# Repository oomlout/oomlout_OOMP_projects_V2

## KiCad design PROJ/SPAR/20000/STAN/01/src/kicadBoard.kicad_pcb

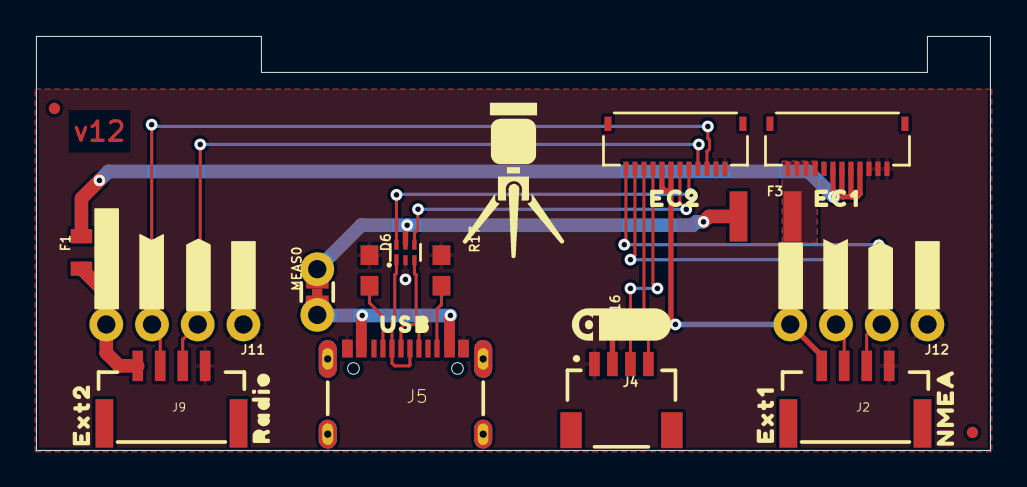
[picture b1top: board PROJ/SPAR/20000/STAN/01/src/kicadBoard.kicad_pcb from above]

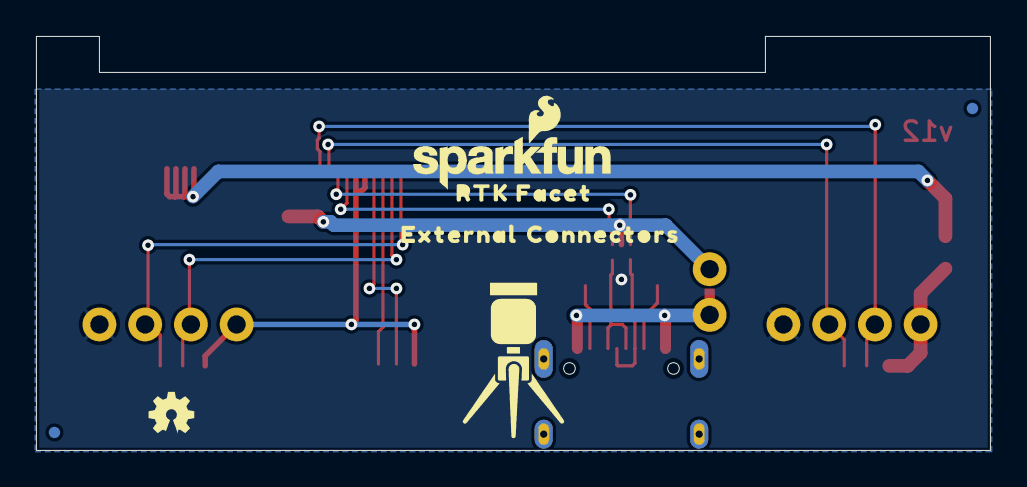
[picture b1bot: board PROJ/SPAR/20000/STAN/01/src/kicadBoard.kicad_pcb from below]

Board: 2 copper layers, 53.0 x 23.0 mm, 42 parts (8 on the bottom side), 19 nets.

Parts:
D6: PRTR5V0U2F; SOT886
F1: 6V 0.5A; 0805
F3: 6V/2A; 1210
FRAME1: FRAME-LETTER; CREATIVE_COMMONS
J1, J6: FPC_12_0.5MM_BACKFLIP; FPC_12_DOUBLESIDED_BACKFLIP
J2, J9: JST-4-SMD-1.25MM-LOCKING
J4: Qwiic Right Angle; JST04_1MM_RA
J5: u-blox USB; USB-C-16P-2LAYER-PADS
J11, J12: 1X04_NO_SILK
JP21, JP61, JP71, JP81: FIDUCIALUFIDUCIAL; FIDUCIAL-MICRO
LOGO1: OSHW-LOGOMINI; OSHW-LOGO-MINI
LOGO2: SFE_LOGO_NAME_FLAME.1_INCH; SFE_LOGO_NAME_FLAME_.1
LOGO3: QWIIC_LOGO_CONNECTOR; QWIIC_5.5MM
MEAS0: COMBO-JUMPER_2_NC_TRACE
R16, R17: 5.1k; 0603
U$1: USB0
U$2: CONNECTORS1
U$3, U$13: RTK5#SVG0
U$4: EXT10
U$5: #3V3#0
U$6: EXT22
U$7: NMEA1
U$8: EC10
U$9: EXTERNAL0
U$11: EC21
U$12: RADIO3
U$14: RTK_FACET0
U$23: #3#5#5V#0
U$38, U$82: #GND#0
U$39: #RX2#2
U$40: #TX2#1
U$65: #TX1#1
U$68: #RX1#2

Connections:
3.3V: J2.1, J4.2, J6.7, J6.8, J12.4
CC1: J5.A5, R17.2
CC2: J5.B5, R16.2
ESP_21/SDA: J4.3, J6.9
ESP_22/SCL: J4.4, J6.10
EXTERNAL_SERIAL1_RXI: J2.3, J6.12, J12.2
EXTERNAL_SERIAL1_TXO: J2.2, J6.11, J12.3
GND: D6.2, J1.1, J1.2, J1.3, J2.4, J4.1, J5.GND, J5.GND2, J5.SHLD1, J5.SHLD2, J5.SHLD3, J5.SHLD4, J6.1, J6.2, J9.4, J11.1, J12.1, R16.1, R17.1
unnamed: F1.1, J9.1, J11.4
USB1_D_M: D6.1, J5.A7, J5.B7
USB1_D_P: D6.3, J5.A6, J5.B6
USB_DM: D6.6, J6.5
USB_DP: D6.4, J6.6
VIN: J5.VBUS1, J5.VBUS2, MEAS0.1, MEAS0.3
VIN1: D6.5, F3.1, MEAS0.2, MEAS0.4
V_BATT: F1.2, J1.4, J1.5, J1.6, J1.7
V_USB: F3.2, J1.9, J1.10, J1.11, J1.12
ZED-RXI2: J6.4, J9.3, J11.2
ZED-TXO2: J6.3, J9.2, J11.3

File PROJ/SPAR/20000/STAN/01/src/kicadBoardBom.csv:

"Id";"Designator";"Package";"Quantity";"Designation";"Supplier and ref";
1;"U$82,U$38";"#GND#0";2;"";;;
2;"R17,R16";"0603";2;"5.1k";;;
3;"J11,J12";"1X04_NO_SILK";2;"";;;
4;"U$12";"RADIO3";1;"";;;
5;"F1";"0805";1;"6V 0.5A";;;
6;"MEAS0";"COMBO-JUMPER_2_NC_TRACE";1;"";;;
7;"U$68";"#RX1#2";1;"";;;
8;"D6";"SOT886";1;"PRTR5V0U2F";;;
9;"LOGO3";"QWIIC_5.5MM";1;"QWIIC_LOGO_CONNECTOR";;;
10;"J9,J2";"JST-4-SMD-1.25MM-LOCKING";2;"";;;
11;"J1,J6";"FPC_12_DOUBLESIDED_BACKFLIP";2;"FPC_12_0.5MM_BACKFLIP";;;
12;"U$39";"#RX2#2";1;"";;;
13;"FRAME1";"CREATIVE_COMMONS";1;"FRAME-LETTER";;;
14;"U$8";"EC10";1;"";;;
15;"J5";"USB-C-16P-2LAYER-PADS";1;"u-blox USB";;;
16;"U$11";"EC21";1;"";;;
17;"JP21,JP61,JP71,JP81";"FIDUCIAL-MICRO";4;"FIDUCIALUFIDUCIAL";;;
18;"U$23";"#3#5#5V#0";1;"";;;
19;"U$40";"#TX2#1";1;"";;;
20;"U$5";"#3V3#0";1;"";;;
21;"U$3,U$13";"RTK5#SVG0";2;"";;;
22;"J4";"JST04_1MM_RA";1;"Qwiic Right Angle";;;
23;"U$65";"#TX1#1";1;"";;;
24;"U$4";"EXT10";1;"";;;
25;"U$1";"USB0";1;"";;;
26;"U$6";"EXT22";1;"";;;
27;"F3";"1210";1;"6V/2A";;;
28;"U$7";"NMEA1";1;"";;;
29;"LOGO2";"SFE_LOGO_NAME_FLAME_.1";1;"SFE_LOGO_NAME_FLAME.1_INCH";;;
30;"U$2";"CONNECTORS1";1;"";;;
31;"U$14";"RTK_FACET0";1;"";;;
32;"LOGO1";"OSHW-LOGO-MINI";1;"OSHW-LOGOMINI";;;
33;"U$9";"EXTERNAL0";1;"";;;

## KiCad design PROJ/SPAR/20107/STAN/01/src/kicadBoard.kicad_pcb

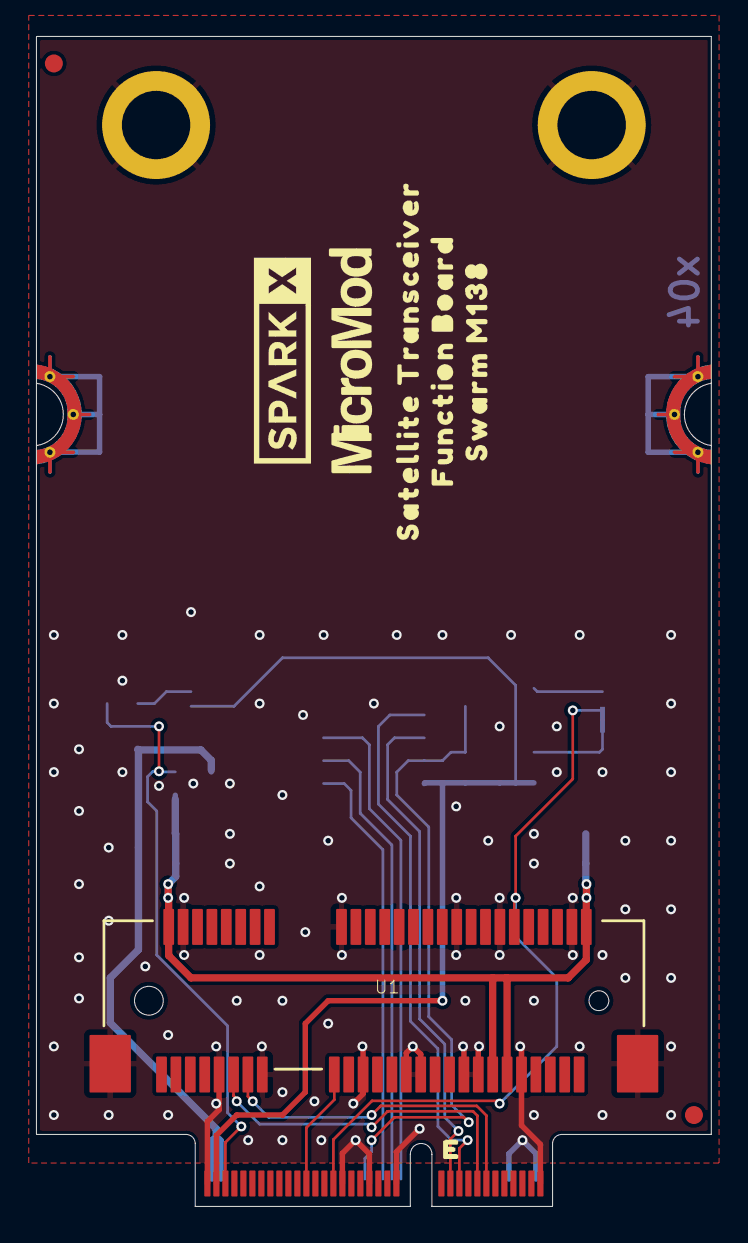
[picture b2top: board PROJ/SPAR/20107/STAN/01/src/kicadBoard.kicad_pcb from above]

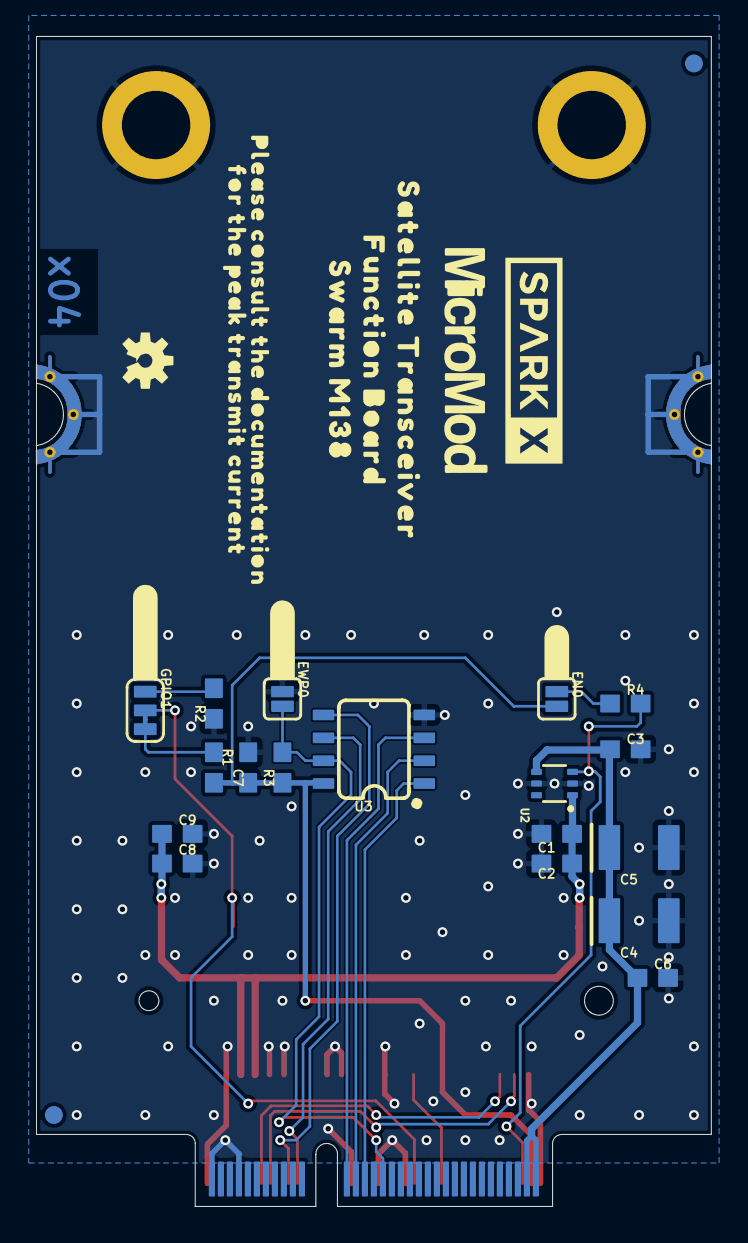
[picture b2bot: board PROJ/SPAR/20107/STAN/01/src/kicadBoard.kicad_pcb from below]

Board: 2 copper layers, 37.5 x 65.0 mm, 44 parts (31 on the bottom side), 18 nets.

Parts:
C1, C9: 10uF; 0603
C2, C3, C6, C7, C8: 0.1uF; 0603
C4, C5: 100uF; EIA3528
EN0: JUMPER-SMT_2_NO_SILK; SMT-JUMPER_2_NO_SILK
EWP0: JUMPER-SMT_2_NO_SILK; SMT-JUMPER_2_NO_SILK
FD1, FD2, FD3, FD4: FIDUCIAL1X2; FIDUCIAL-1X2
FRAME1: FRAME-LETTER; CREATIVE_COMMONS
GPIO1: JUMPER-SMT_3_1-NC_TRACE_SILK; SMT-JUMPER_3_1-NC_TRACE_SILK
H5, H6: STAND-OFF-REFLOW-M2.5_1.5MM_TALL; STAND-OFF-REFLOW-M2.5
J3: MICROMOD_FUNCTION_STANDARD; M.2-CARD-E-22_FUNCTION_STANDARD
LOGO1: SPECIAL_INSTRUCTIONS-ORDERING; ORDERING_INSTRUCTIONS
LOGO2: OSHW-LOGOS; OSHW-LOGO-S
R1, R2, R3, R4: 100k; 0603
U1: SWARM_M138_TRANSCEIVER_MAIN; M.2-SWARM-M138-A
U2: MIC94064YC6; SC-70-6
U3: EEPROM; SO08
U$1, U$2: SPARKX-LOGO5; SPARKX-LARGE
U$3, U$7: FUNCTION_BOARD0
U$4, U$5: SATELLITE_TRANSCEIVER0
U$6: PLEASE_CONSULT_THE_DOCUMENTATION0
U$8: #EWP#0
U$9, U$10: MICROMOD_LOGO_.5
U$11: #EN#0
U$19: #GPIO1#0
U$31: FOR_THE_PEAK_TRANSMIT_CURRENT1
U$40, U$41: SWARM_M1381

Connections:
3.3V: C7.1, EN0.2, J3.73, R1.2, R3.1, U3.8
A0: J3.36, U3.1
A1: J3.34, U3.2
A2: J3.32, U3.3
EWP: EWP0.2, J3.40, R3.2, U3.7
GND: C1.2, C2.2, C3.2, C4.C, C5.C, C6.2, C7.2, C8.2, C9.2, EWP0.1, H5.1, H6.1, J3.1, J3.2, J3.8, J3.33, J3.39, J3.45, J3.75, J3.GND1, J3.GND2, J3.GND3, J3.GND4, J3.GND5, J3.GND6, R2.1, U1.4, U1.9, U1.15, U1.18, U1.21, U1.26, U1.27, U1.29, U1.34, U1.35, U1.37, U1.40, U1.43, U1.50, U1.A1, U1.A2, U2.2, U2.5, U3.4
GPIO1: GPIO1.2, J3.47, U1.42
unnamed: EN0.1, R4.1
unnamed: GPIO1.3, R1.1
unnamed: GPIO1.1, R2.2
PWR_EN: J3.71, R4.2, U2.3
RXI: J3.15, U1.11
SCL: J3.21, U3.6
SDA: J3.19, U3.5
TX/~RX: J3.53, U1.17
TXO: J3.13, U1.13
VCC: C3.1, C4.A, C5.A, C6.1, J3.72, J3.74, U2.4
VIN: C1.1, C2.1, C8.1, C9.1, U1.2, U1.39, U1.41, U1.52, U2.1

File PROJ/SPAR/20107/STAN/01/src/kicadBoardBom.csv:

"Id";"Designator";"Package";"Quantity";"Designation";"Supplier and ref";
1;"H6,H5";"STAND-OFF-REFLOW-M2.5";2;"STAND-OFF-REFLOW-M2.5_1.5MM_TALL";;;
2;"FD1,FD3,FD4,FD2";"FIDUCIAL-1X2";4;"FIDUCIAL1X2";;;
3;"J3";"M.2-CARD-E-22_FUNCTION_STANDARD";1;"MICROMOD_FUNCTION_STANDARD";;;
4;"LOGO1";"ORDERING_INSTRUCTIONS";1;"SPECIAL_INSTRUCTIONS-ORDERING";;;
5;"U$40,U$41";"SWARM_M1381";2;"";;;
6;"U$9,U$10";"MICROMOD_LOGO_.5";2;"";;;
7;"FRAME1";"CREATIVE_COMMONS";1;"FRAME-LETTER";;;
8;"U$2,U$1";"SPARKX-LARGE";2;"SPARKX-LOGO5";;;
9;"U1";"M.2-SWARM-M138-A";1;"SWARM_M138_TRANSCEIVER_MAIN";;;
10;"U$4,U$5";"SATELLITE_TRANSCEIVER0";2;"";;;
11;"U$3,U$7";"FUNCTION_BOARD0";2;"";;;
12;"LOGO2";"OSHW-LOGO-S";1;"OSHW-LOGOS";;;
13;"GPIO1";"SMT-JUMPER_3_1-NC_TRACE_SILK";1;"JUMPER-SMT_3_1-NC_TRACE_SILK";;;
14;"R3,R2,R1,R4";"0603";4;"100k";;;
15;"C3,C7,C6,C8,C2";"0603";5;"0.1uF";;;
16;"U2";"SC-70-6";1;"MIC94064YC6";;;
17;"U$19";"#GPIO1#0";1;"";;;
18;"U$6";"PLEASE_CONSULT_THE_DOCUMENTATION0";1;"";;;
19;"C4,C5";"EIA3528";2;"100uF";;;
20;"EN0,EWP0";"SMT-JUMPER_2_NO_SILK";2;"JUMPER-SMT_2_NO_SILK";;;
21;"U$8";"#EWP#0";1;"";;;
22;"U$31";"FOR_THE_PEAK_TRANSMIT_CURRENT1";1;"";;;
23;"C9,C1";"0603";2;"10uF";;;
24;"U3";"SO08";1;"EEPROM";;;
25;"U$11";"#EN#0";1;"";;;

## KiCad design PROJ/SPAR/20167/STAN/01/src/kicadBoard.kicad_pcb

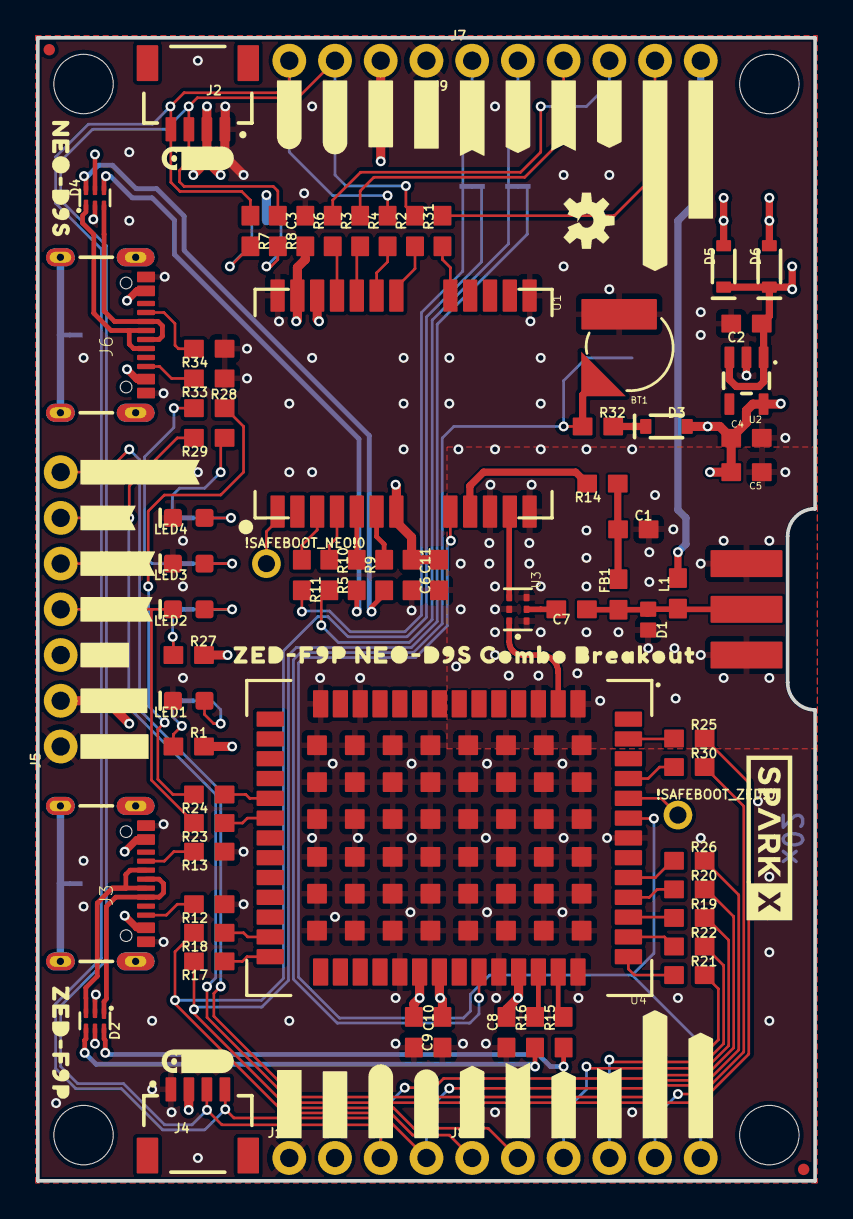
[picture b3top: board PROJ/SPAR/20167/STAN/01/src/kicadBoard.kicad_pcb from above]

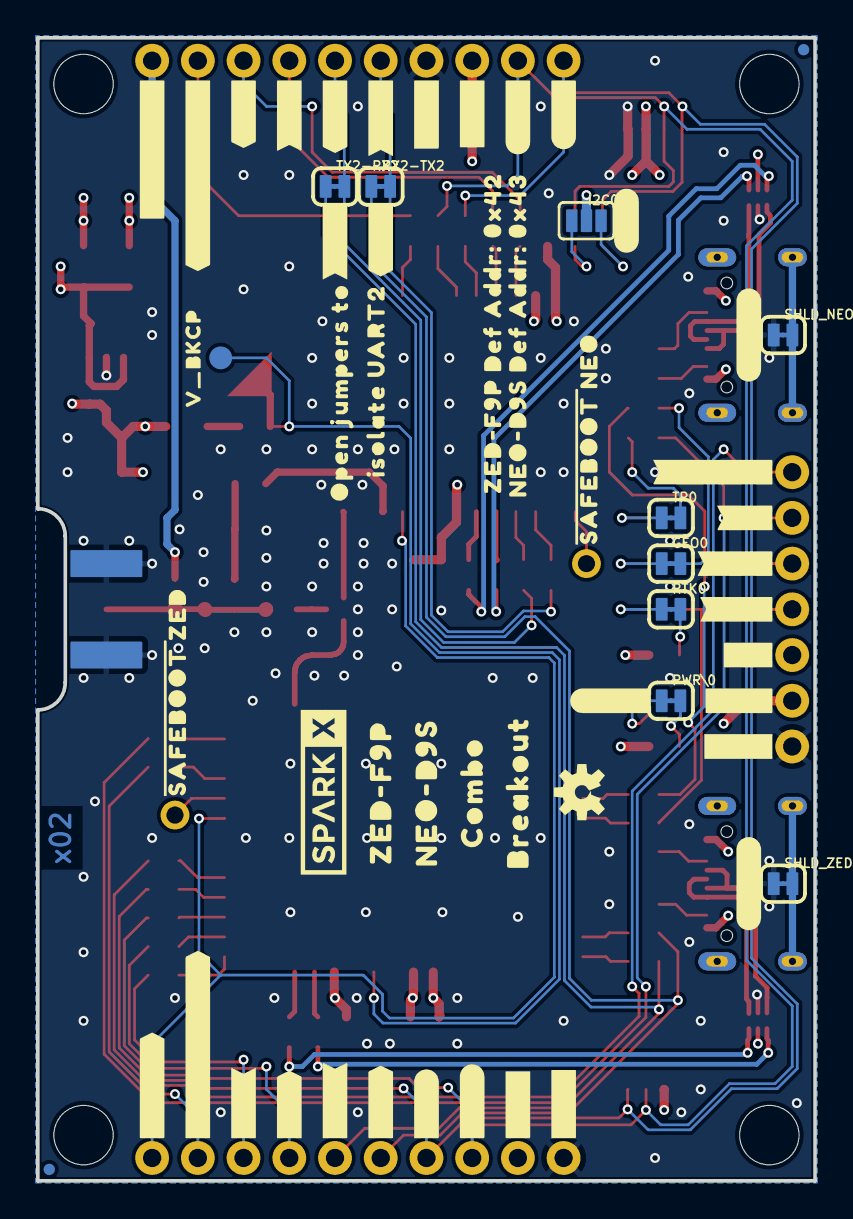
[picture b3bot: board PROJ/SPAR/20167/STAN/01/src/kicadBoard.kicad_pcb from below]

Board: 4 copper layers, 43.2 x 63.5 mm, 174 parts (58 on the bottom side), 79 nets.

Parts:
!SAFEBOOT_NEO!0: TEST-POINTPOGO_PTH; 1X01_NO_SILK
!SAFEBOOT_ZED!0: TEST-POINTPOGO_PTH; 1X01_NO_SILK
BT1: RELOWABLE_BATTERY_MS421R; MS421R_IV03E
C1, C7: 47pF; 0603
C2, C3, C4, C6, C8, C9: 1.0uF; 0603
C5, C10, C11: 0.1uF; 0603
D1: PESD0402-0402; 0402
D2, D4: PRTR5V0U2F; SOT886
D3: 0.5A/40V/420mV; SOD-323
D5, D6: 1A/23V/620mV; SOD-323
FB1: 30Ω/1.8A; 0603
FRAME2: FRAME-LEDGER; CREATIVE_COMMONS
GEO0: JUMPER-SMT_2_NC_TRACE_SILK; SMT-JUMPER_2_NC_TRACE_SILK
I2C0: JUMPER-SMT_3_NO_SILK; SMT-JUMPER_3_NO_SILK
J1: ANTENNA-SMA-GROUNDEDEDGE_SMA; SMA-EDGE
J2, J4: Qwiic Right Angle; JST04_1MM_RA
J3, J6: USB Female Type C Connector; USB-C-16P_4LAYER-PADS
J5: 1X07_NO_SILK
J7, J8: 1X06_NO_SILK
J9, J10: 1X04_NO_SILK
JP21, JP61, JP71, JP81: FIDUCIALUFIDUCIAL; MICRO-FIDUCIAL
JP31, JP41, JP91, JP101: STAND-OFF
L1: DNP; 0603_NO-CREAM
LED1: RED; LED-0603
LED2, LED3, LED4: BLUE; LED-0603
LOGO1, LOGO4: OSHW-LOGOS; OSHW-LOGO-S
LOGO5: SPECIAL_INSTRUCTIONS-ORDERING; ORDERING_INSTRUCTIONS
PWR\0: JUMPER-SMT_2_NC_TRACE_SILK; SMT-JUMPER_2_NC_TRACE_SILK
R1, R27, R28, R29: 1k; 0603
R2, R3, R4, R5, R6, R11, R17, R18, R19, R20, R21, R22, R23, R24, R25, R26, R30, R31: 33; 0603
R7, R8: 2.2k; 0603
R9, R10, R15, R16: 27; 0603
R12, R13, R33, R34: 5.1k; 0603
R14: 10; 0603
R32: 3.3k; 0603
RTK0: JUMPER-SMT_2_NC_TRACE_SILK; SMT-JUMPER_2_NC_TRACE_SILK
RX2-TX2: JUMPER-SMT_2_NC_TRACE_SILK; SMT-JUMPER_2_NC_TRACE_SILK
SHLD_NEO0: JUMPER-SMT_2_NC_TRACE_SILK; SMT-JUMPER_2_NC_TRACE_SILK
SHLD_ZED0: JUMPER-SMT_2_NC_TRACE_SILK; SMT-JUMPER_2_NC_TRACE_SILK
TP0: JUMPER-SMT_2_NC_TRACE_SILK; SMT-JUMPER_2_NC_TRACE_SILK
TX2-RX2: JUMPER-SMT_2_NC_TRACE_SILK; SMT-JUMPER_2_NC_TRACE_SILK
U1: U-BLOX_NEO-D9S-00B; NEO-M9N_M8T_M8U_D9S
U2: 3.3V; SOT23-5
U3: POWER-DIVIDER; PD0922J5050S2HF_ANA
U4: U-BLOX_ZED-F9P; ZED-F9P
U$1, U$2, U$3: #GND#0
U$4, U$5, U$6: #GND#1
U$7, U$53: #SHLD#0
U$8, U$10: #SDA#0
U$9, U$13: #SCL#0
U$11, U$12: #SDA#1
U$14, U$38: QWIIC_4MM
U$15, U$30: #SCL#1
U$16: #RTK#0
U$17: #RTK#1
U$18: #GEO#0
U$19: #GEO#1
U$20: #5V#0
U$21: #5V#6
U$22, U$23, U$56: #3V3#0
U$24, U$25, U$70: #3V3#4
U$26: #TP#0
U$27: #TP#1
U$28: #TX_RDY#0
U$29: #TX_RDY#1
U$31, U$39, U$40: #TX2#0
U$32, U$34, U$35: #RX2#0
U$33: OPEN_JUMPERS_TO0
U$36, U$37: #RX2#3
U$41, U$42: #TX2#3
U$43, U$44: #RX1#0
U$45: ##RESET##0
U$46: ##RESET##1
U$47: #EXT_INT#0
U$48: #EXT_INT_ZED#0
U$49, U$50: #RX1#2
U$51, U$57: #TX1#0
U$52: #I�C#0
U$54: ISOLATE_UART21
U$55: NEO#D9S0
U$58: #ANT_PWR#0
U$59: #ANT_PWR#1
U$60, U$61: #TX1#2
U$62: #EXT_INT_NEO#0
U$63: #EXT_INT_NEO#1
U$64: ZED#F9P0
U$65: ZED#F9P10
U$66: NEO#D9S10
U$67: COMBO10
U$68: BREAKOUT11
U$69: #PWR#0
U$71: #SAFEBOOT#_NEO0
U$72: #SAFEBOOT#_ZED0
U$73: NEO#D9S_DEF_ADDR#_0X4310
U$74: ZED#F9P_DEF_ADDR#_0X420
U$75: ZED#F9P_NEO#D9S_COMBO_BREAKOUT0
U$76: V_BKCP0
U$77, U$78: SPARKX-LOGO4; SPARKX-MEDIUM
V_BKCP0: TEST-POINT3X5; PAD.03X.05

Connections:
3.3V: C3.1, C4.1, C5.2, C6.1, C8.2, C9.1, C10.2, C11.2, D3.A, I2C0.2, J2.2, J4.2, J5.2, J9.2, J10.2, R1.2, R27.2, U1.7, U1.22, U1.23, U2.5, U4.33, U4.34, U4.38
5V: C2.1, D5.C, D6.C, J5.3, U2.1, U2.3
ANT: C7.2, U3.2
ANT_NEO: U1.11, U3.4
ANT_PWR: J7.6, L1.2
ANT_VCC: C1.1, FB1.2, R14.1
ANT_ZED: U3.6, U4.2
D+_NEO: D4.6, R9.1
D+_ZED: D2.6, R15.1
D-_NEO: D4.4, R10.1
D-_ZED: D2.4, R16.1
EXT_INT_NEO: J7.5, R31.2
EXT_INT_ZED: J8.5, R30.2
GEO: J5.5, R24.2, R28.2
GND: BT1.-, C1.2, C2.2, C3.2, C4.2, C5.1, C6.2, C8.1, C9.2, C10.1, C11.1, D1.2, D2.2, D4.2, J1.GND@0, J1.GND@1, J1.GND@2, J1.GND@3, J2.1, J3.GND, J3.GND2, J4.1, J5.1, J6.GND, J6.GND2, J9.1, J10.1, LED1.C, LED3.C, LED4.C, R12.1, R13.1, R33.1, R34.1, SHLD_NEO0.1, SHLD_ZED0.1, U1.10, U1.12, U1.13, U1.24, U2.2, U3.1, U3.3, U3.5, U4.1, U4.3, U4.12, U4.14, U4.32, U4.37, U4.41, U4.48, U4.55, U4.56, U4.57, U4.58, U4.59, U4.60, U4.61, U4.62, U4.63, U4.64, U4.65, U4.66, U4.67, U4.68, U4.69, U4.70, U4.71, U4.72, U4.73, U4.74, U4.75, U4.76, U4.77, U4.78, U4.79, U4.80, U4.81, U4.82, U4.83, U4.84, U4.85, U4.86, U4.87, U4.88, U4.89, U4.90, U4.91, U4.92, U4.93, U4.94, U4.95, U4.96, U4.97, U4.98, U4.99, U4.100, U4.101, U4.102
unnamed: PWR\0.2, R1.1
unnamed: R3.1, U1.20
unnamed: R2.1, U1.18
unnamed: R4.1, U1.19
unnamed: I2C0.1, R8.2
unnamed: R6.1, U1.21
unnamed: J3.B5, R12.2
unnamed: I2C0.3, R7.2
unnamed: J3.A5, R13.2
unnamed: LED1.A, PWR\0.1
unnamed: R9.2, U1.6
unnamed: R10.2, U1.5
unnamed: D3.C, R32.2
unnamed: R11.1, U1.3
unnamed: R5.1, U1.4
unnamed: R15.2, U4.40
unnamed: R16.2, U4.39
unnamed: R19.1, U4.44
unnamed: R20.1, U4.45
unnamed: R21.1, U4.42
unnamed: R22.1, U4.43
unnamed: R26.1, U4.46
unnamed: LED2.A, RTK0.1
unnamed: R17.1, U4.27
unnamed: R18.1, U4.26
unnamed: GEO0.1, LED3.A
unnamed: LED4.A, TP0.1
unnamed: R27.1, RTK0.2
unnamed: GEO0.2, R28.1
unnamed: R29.1, TP0.2
unnamed: R30.1, U4.51
unnamed: R31.1, U1.17
unnamed: J6.B5, R33.2
unnamed: J6.A5, R34.2
unnamed: R23.1, U4.20
unnamed: R24.1, U4.19
unnamed: R25.1, U4.53
RTK: J5.4, LED2.C, R23.2
RXD1_NEO: J7.4, R6.2
RXD1_ZED: J8.3, R22.2
RXD2_NEO: J7.2, R5.2, TX2-RX2.2
RXD2_ZED: J8.1, R18.2, RX2-TX2.1
SCL: J2.4, J4.4, J9.4, J10.4, R4.2, R7.1, R20.2
SDA: J2.3, J4.3, J9.3, J10.3, R2.2, R8.1, R19.2
SHIELD_NEO: J6.SHLD1, J6.SHLD2, J6.SHLD3, J6.SHLD4, SHLD_NEO0.2
SHIELD_ZED: J3.SHLD1, J3.SHLD2, J3.SHLD3, J3.SHLD4, SHLD_ZED0.2
SMA: C7.1, D1.1, FB1.1, J1.SIG, L1.1
TP: J5.6, R25.2, R29.2
TXD1_NEO: J7.3, R3.2
TXD1_ZED: J8.4, R21.2
TXD2_NEO: J7.1, R11.2, RX2-TX2.2
TXD2_ZED: J8.2, R17.2, TX2-RX2.1
TX_RDY: J5.7, R26.2
USB_D+: D2.1, J3.A6, J3.B6
USB_D+1: D4.1, J6.A6, J6.B6
USB_D-: D2.3, J3.A7, J3.B7
USB_D-1: D4.3, J6.A7, J6.B7
VCC_RF: R14.2, U1.9
V_BKCP: BT1.+, R32.1, U4.36, V_BKCP0.1
V_USB: D2.5, D5.A, J3.VBUS1, J3.VBUS2
V_USB_2: D4.5, D6.A, J6.VBUS1, J6.VBUS2
~RESET: J8.6, U1.8, U4.49
~SAFEBOOT_NEO: !SAFEBOOT_NEO!0.1, U1.1
~SAFEBOOT_ZED: !SAFEBOOT_ZED!0.1, U4.50

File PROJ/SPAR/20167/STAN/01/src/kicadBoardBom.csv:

"Id";"Designator";"Package";"Quantity";"Designation";"Supplier and ref";
1;"U$66";"NEO#D9S10";1;"";;;
2;"U$28";"#TX_RDY#0";1;"";;;
3;"R19,R5,R18,R25,R22,R4,R20,R23,R17,R21,R3,R6,R31,R26,R11,R24,R2,R30";"0603";18;"33";;;
4;"U$43,U$44";"#RX1#0";2;"";;;
5;"C7,C1";"0603";2;"47pF";;;
6;"LOGO1,LOGO4";"OSHW-LOGO-S";2;"OSHW-LOGOS";;;
7;"C11,C10,C5";"0603";3;"0.1uF";;;
8;"J7,J8";"1X06_NO_SILK";2;"";;;
9;"C8,C3,C9,C4,C6,C2";"0603";6;"1.0uF";;;
10;"U2";"SOT23-5";1;"3.3V";;;
11;"!SAFEBOOT_NEO!0,!SAFEBOOT_ZED!0";"1X01_NO_SILK";2;"TEST-POINTPOGO_PTH";;;
12;"R1,R29,R28,R27";"0603";4;"1k";;;
13;"U$22,U$56,U$23";"#3V3#0";3;"";;;
14;"U$36,U$37";"#RX2#3";2;"";;;
15;"U$1,U$2,U$3";"#GND#0";3;"";;;
16;"J4,J2";"JST04_1MM_RA";2;"Qwiic Right Angle";;;
17;"BT1";"MS421R_IV03E";1;"RELOWABLE_BATTERY_MS421R";;;
18;"FB1";"0603";1;"30Ω/1.8A";;;
19;"R15,R10,R9,R16";"0603";4;"27";;;
20;"U$11,U$12";"#SDA#1";2;"";;;
21;"U$75";"ZED#F9P_NEO#D9S_COMBO_BREAKOUT0";1;"";;;
22;"U4";"ZED-F9P";1;"U-BLOX_ZED-F9P";;;
23;"U$14,U$38";"QWIIC_4MM";2;"";;;
24;"JP41,JP101,JP91,JP31";"STAND-OFF";4;"STAND-OFF";;;
25;"U$49,U$50";"#RX1#2";2;"";;;
26;"LED2,LED3,LED4";"LED-0603";3;"BLUE";;;
27;"U$26";"#TP#0";1;"";;;
28;"J1";"SMA-EDGE";1;"ANTENNA-SMA-GROUNDEDEDGE_SMA";;;
29;"JP61,JP21,JP81,JP71";"MICRO-FIDUCIAL";4;"FIDUCIALUFIDUCIAL";;;
30;"U$47";"#EXT_INT#0";1;"";;;
31;"U$16";"#RTK#0";1;"";;;
32;"U$45";"##RESET##0";1;"";;;
33;"R12,R13,R34,R33";"0603";4;"5.1k";;;
34;"D6,D5";"SOD-323";2;"1A/23V/620mV";;;
35;"D3";"SOD-323";1;"0.5A/40V/420mV";;;
36;"R32";"0603";1;"3.3k";;;
37;"R8,R7";"0603";2;"2.2k";;;
38;"J5";"1X07_NO_SILK";1;"";;;
39;"U$34,U$35,U$32";"#RX2#0";3;"";;;
40;"J6,J3";"USB-C-16P_4LAYER-PADS";2;"USB Female Type C Connector";;;
41;"U$20";"#5V#0";1;"";;;
42;"U$39,U$40,U$31";"#TX2#0";3;"";;;
43;"LOGO5";"ORDERING_INSTRUCTIONS";1;"SPECIAL_INSTRUCTIONS-ORDERING";;;
44;"U$18";"#GEO#0";1;"";;;
45;"U$25,U$24,U$70";"#3V3#4";3;"";;;
46;"U$13,U$9";"#SCL#0";2;"";;;
47;"R14";"0603";1;"10";;;
48;"U$59";"#ANT_PWR#1";1;"";;;
49;"U$8,U$10";"#SDA#0";2;"";;;
50;"L1";"0603_NO-CREAM";1;"DNP";;;
51;"D1";"0402";1;"PESD0402-0402";;;
52;"U$77,U$78";"SPARKX-MEDIUM";2;"SPARKX-LOGO4";;;
53;"U$41,U$42";"#TX2#3";2;"";;;
54;"U1";"NEO-M9N_M8T_M8U_D9S";1;"U-BLOX_NEO-D9S-00B";;;
55;"D4,D2";"SOT886";2;"PRTR5V0U2F";;;
56;"U3";"PD0922J5050S2HF_ANA";1;"POWER-DIVIDER";;;
57;"U$62";"#EXT_INT_NEO#0";1;"";;;
58;"U$30,U$15";"#SCL#1";2;"";;;
59;"U$65";"ZED#F9P10";1;"";;;
60;"LED1";"LED-0603";1;"RED";;;
61;"J10,J9";"1X04_NO_SILK";2;"";;;
62;"U$60,U$61";"#TX1#2";2;"";;;
63;"U$4,U$6,U$5";"#GND#1";3;"";;;
64;"U$51,U$57";"#TX1#0";2;"";;;
65;"FRAME2";"CREATIVE_COMMONS";1;"FRAME-LEDGER";;;
66;"U$52";"#I�C#0";1;"";;;
67;"U$33";"OPEN_JUMPERS_TO0";1;"";;;
68;"RTK0,SHLD_NEO0,TP0,TX2-RX2,RX2-TX2,GEO0,PWR\0,SHLD_ZED0";"SMT-JUMPER_2_NC_TRACE_SILK";8;"JUMPER-SMT_2_NC_TRACE_SILK";;;
69;"U$69";"#PWR#0";1;"";;;
70;"V_BKCP0";"PAD.03X.05";1;"TEST-POINT3X5";;;
71;"I2C0";"SMT-JUMPER_3_NO_SILK";1;"JUMPER-SMT_3_NO_SILK";;;
72;"U$54";"ISOLATE_UART21";1;"";;;
73;"U$72";"#SAFEBOOT#_ZED0";1;"";;;
74;"U$58";"#ANT_PWR#0";1;"";;;
75;"U$64";"ZED#F9P0";1;"";;;
76;"U$27";"#TP#1";1;"";;;
77;"U$71";"#SAFEBOOT#_NEO0";1;"";;;
78;"U$63";"#EXT_INT_NEO#1";1;"";;;
79;"U$29";"#TX_RDY#1";1;"";;;
80;"U$76";"V_BKCP0";1;"";;;
81;"U$68";"BREAKOUT11";1;"";;;
82;"U$73";"NEO#D9S_DEF_ADDR#_0X4310";1;"";;;
83;"U$21";"#5V#6";1;"";;;
84;"U$55";"NEO#D9S0";1;"";;;
85;"U$48";"#EXT_INT_ZED#0";1;"";;;
86;"U$46";"##RESET##1";1;"";;;
87;"U$67";"COMBO10";1;"";;;
88;"U$53,U$7";"#SHLD#0";2;"";;;
89;"U$19";"#GEO#1";1;"";;;
90;"U$17";"#RTK#1";1;"";;;
91;"U$74";"ZED#F9P_DEF_ADDR#_0X420";1;"";;;

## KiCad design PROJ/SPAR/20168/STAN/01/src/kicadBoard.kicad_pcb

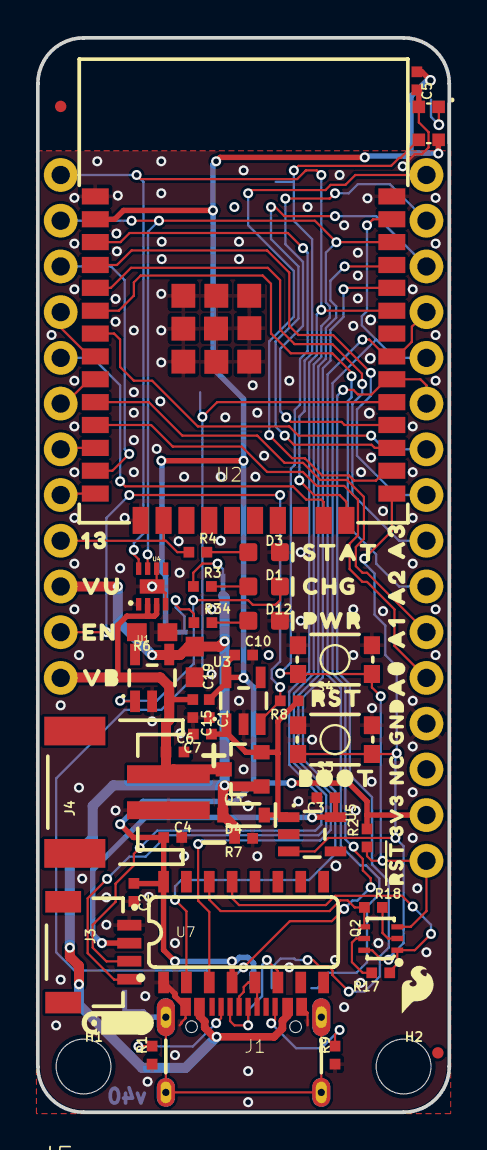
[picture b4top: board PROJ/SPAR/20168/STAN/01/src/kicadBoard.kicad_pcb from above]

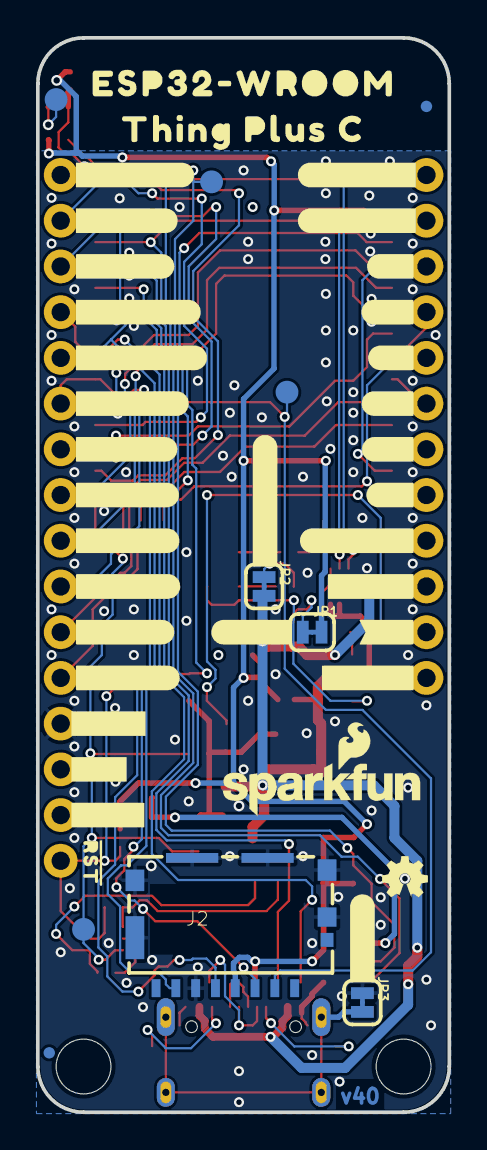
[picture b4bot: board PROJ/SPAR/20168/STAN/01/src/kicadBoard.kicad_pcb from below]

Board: 2 copper layers, 22.9 x 59.7 mm, 110 parts (46 on the bottom side), 51 nets.

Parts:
C1, C4: 10uF; 0402-TIGHT
C2, C5, C15: 0.1uF; 0402-TIGHT
C3, C7, C10: 1.0uF; 0402-TIGHT
C6: 4.7uF; 0402-TIGHT
C19: 4.7uF; 0603
D1: Yellow; LED-0603
D3: BLUE; LED-0603
D4: 3A/10V/280mV; SOD-323
D5: WS2812; WS2812-2020
D12: RED; LED-0603
FD1, FD2, FD3, FD4: FIDUCIALUFIDUCIAL; FIDUCIAL-MICRO
FRAME1: FRAME-LEDGER; CREATIVE_COMMONS
H1, H2: STAND-OFFTIGHT; STAND-OFF-TIGHT
J1: USB-C-16P-2LAYER-PADS
J2: MICRO-SDFRICTION; MICROSD_TINY
J3: QWIIC_RA; JST04_1MM_RA
J4: JST-2-SMD
J5: THING_PLUS_LOGICAL; THING_PLUS
JP1, JP2, JP3: JUMPER-SMT_2_NC_TRACE_SILK; SMT-JUMPER_2_NC_TRACE_SILK
LOGO1: SFE_LOGO_NAME_FLAME.1_INCH; SFE_LOGO_NAME_FLAME_.1
LOGO2: OSHW-LOGOMINI; OSHW-LOGO-MINI
LOGO4: QWIIC_LOGO_4MM; QWIIC_4MM
Q2: MBT3904DW1T1; SC70-6
Q3: 20V/4.2A/52mΩ/1.4W; SOT23-3
R2, R7, R8, R17, R18: 10k; 0402-TIGHT
R3, R4, R34: 1k; 0402-TIGHT
R6: 2.0k; 0603
R9, R10: 5.1k; 0402-TIGHT
S3: Boot; TACTILE_SWITCH_SMD_4.6X2.8MM
S4: Reset; TACTILE_SWITCH_SMD_4.6X2.8MM
TP1, TP2, TP3, TP4: TEST-POINT3X5; PAD.03X.05
U1: MCP73831; SOT23-5
U2: ESP-WROOM-3232D-NARROW; ESP-WROOM-32D-NARROW
U3, U5: XC6222B331MR-G; SOT23-5
U4: MAX17048; DFN-8
U7: CH340C; SO016
U$1: SFE_LOGO_FLAME_STOP_.1
U$2: #23#PICO#0
U$3: #19#POCI#0
U$4: #4#FREE#0
U$5: #CHG_LED#0
U$6: ESP32#WROOM0
U$7: THING_PLUS_C0
U$8: #SHLD#0
U$9: #_GND#0
U$10: #_NC#0
U$11: #_3V3#0
U$12: SFE_LOGO_FLAME_.1
U$23: 3V30
U$24: CHG1
U$25: PWR2
U$26: STAT0
U$68: A03
U$69: A12
U$70: A21
U$71: A30
U$72: #17#TX#0
U$73: VB1
U$74: EN3
U$75: GND1
U$76: VU0
U$77: 130
U$78: BOOT0
U$79, U$109: #RST#0
U$80: RST0
U$81: #16#RX#0
U$83: #18#SCK#0
U$84: #35#A5#0
U$85: #36#A4#0
U$86: #25#A1#2
U$87: #26#A0#3
U$88: #34#A2#1
U$89: #39#A3#0
U$90: #12#4
U$91: #14#9
U$92: #15#7
U$93: #27#5
U$94: #32#8
U$95: #33#6
U$96: #EN#1
U$97: #VBAT#0
U$98: #VUSB#2
U$99: #13#LED#0
U$100: #21#SDA#1
U$101: #22#SCL#0
U$102: #PWR#0
U$107: NC0

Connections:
3.3V: C1.1, C2.1, C4.1, C5.1, C10.1, D5.VCC, J2.4, J5.27, JP1.2, R2.2, U2.2, U3.5, U7.4, U7.16
CH340-DTR: Q2.1, R17.1, U7.13
CH340-RTS: Q2.4, R18.1, U7.14
CH340-RX: U2.35, U7.3
CH340-TX: U2.34, U7.2
CHG_LED: D1.A, R3.2
D+: J1.A6, J1.B6, U7.5
D-: J1.A7, J1.B7, U7.6
DTR-10K: Q2.5, R17.2
ESP_0/QPWR: Q2.6, S3.3, S3.4, TP1.1, U2.25, U5.3
ESP_2/RGB_DI: D5.DI, TP3.1, U2.24
ESP_4/TP_FB: J5.13, U2.26
ESP_5/SD_CS: J2.2, TP4.1, U2.29
ESP_12/GPIO1: J5.8, U2.14
ESP_13/GPIO0/LED: J5.9, R4.1, U2.16
ESP_14/GPIO6: J5.3, U2.13
ESP_15/GPIO4: J5.5, U2.23
ESP_16/TP_RX: J5.15, U2.27
ESP_17/TP_TX: J5.14, U2.28
ESP_18/TP_SCK: J2.5, J5.18, U2.30
ESP_19/TP_POCI: J2.7, J5.16, U2.31
ESP_21/TP_SDA: J3.3, J5.1, U2.33, U4.8
ESP_22/TP_SCL: J3.4, J5.2, U2.36, U4.7
ESP_23/TP_PICO: J2.3, J5.17, U2.37
ESP_25/TP_A1: J5.23, U2.10
ESP_26/TP_A0: J5.24, U2.11
ESP_27/GPIO2: J5.7, U2.12
ESP_32/GPIO5: J5.4, U2.8
ESP_33/GPIO3: J5.6, U2.9
ESP_34/TP_A2: J5.22, U2.6
ESP_35/TP_A5: J5.19, U2.7
ESP_36/TP_A4: J5.20, U2.4
ESP_39/TP_A3: J5.21, U2.5
GND: C1.2, C2.2, C3.2, C4.2, C5.2, C6.2, C7.2, C10.2, C15.2, C19.2, D3.C, D5.GND, D12.C, J1.GND, J1.GND2, J2.6, J2.GND1, J2.GND2, J2.GND3, J2.GND4, J2.GND5, J2.GND6, J3.1, J4.1, J5.25, JP3.1, R6.1, R7.1, R9.1, R10.1, S3.1, S3.2, S4.1, S4.2, U1.2, U2.1, U2.15, U2.38, U2.GND1, U2.GNDT1, U2.GNDT2, U2.GNDT3, U2.GNDT4, U2.GNDT5, U2.GNDT6, U2.GNDT7, U2.GNDT8, U3.2, U4.1, U4.4, U4.6, U4.9, U5.2, U7.1
unnamed: JP1.1, R34.1
unnamed: D3.A, R4.2
unnamed: D5.DO, TP2.1
unnamed: JP2.1, R3.1
unnamed: J1.B5, R9.2
unnamed: J1.A5, R10.2
unnamed: D1.C, U1.1
unnamed: J1.SHLD1, J1.SHLD2, J1.SHLD3, J1.SHLD4, JP3.2
unnamed: R6.2, U1.5
unnamed: D12.A, R34.2
QWIIC_PWR: C3.1, J3.2, U5.5
RTS-10K: Q2.2, R18.2
TP_EN: J5.11, R8.2, U3.3
VIN: C7.1, D4.C, Q3.2, R8.1, U3.1, U5.1
V_BATT: C6.1, C15.1, J4.2, J5.12, Q3.3, U1.3, U4.2, U4.3
V_USB: C19.1, D4.A, J1.VBUS1, J1.VBUS2, J5.10, JP2.2, Q3.1, R7.2, U1.4
~RESET: J5.28, Q2.3, R2.1, S4.3, S4.4, U2.3

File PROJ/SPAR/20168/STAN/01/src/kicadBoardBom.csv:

"Id";"Designator";"Package";"Quantity";"Designation";"Supplier and ref";
1;"U$74";"EN3";1;"";;;
2;"U$69";"A12";1;"";;;
3;"C6";"0402-TIGHT";1;"4.7uF";;;
4;"U$78";"BOOT0";1;"";;;
5;"S4";"TACTILE_SWITCH_SMD_4.6X2.8MM";1;"Reset";;;
6;"C5,C2,C15";"0402-TIGHT";3;"0.1uF";;;
7;"U$70";"A21";1;"";;;
8;"R18,R7,R17,R8,R2";"0402-TIGHT";5;"10k";;;
9;"R34,R3,R4";"0402-TIGHT";3;"1k";;;
10;"U$76";"VU0";1;"";;;
11;"D12";"LED-0603";1;"RED";;;
12;"LOGO4";"QWIIC_4MM";1;"QWIIC_LOGO_4MM";;;
13;"U$23";"3V30";1;"";;;
14;"U$80";"RST0";1;"";;;
15;"C4,C1";"0402-TIGHT";2;"10uF";;;
16;"C19";"0603";1;"4.7uF";;;
17;"FRAME1";"CREATIVE_COMMONS";1;"FRAME-LEDGER";;;
18;"D1";"LED-0603";1;"Yellow";;;
19;"C3,C7,C10";"0402-TIGHT";3;"1.0uF";;;
20;"U1";"SOT23-5";1;"MCP73831";;;
21;"H1,H2";"STAND-OFF-TIGHT";2;"STAND-OFFTIGHT";;;
22;"U$24";"CHG1";1;"";;;
23;"J5";"THING_PLUS";1;"THING_PLUS_LOGICAL";;;
24;"R10,R9";"0402-TIGHT";2;"5.1k";;;
25;"J1";"USB-C-16P-2LAYER-PADS";1;"";;;
26;"D4";"SOD-323";1;"3A/10V/280mV";;;
27;"U$77";"130";1;"";;;
28;"U$75";"GND1";1;"";;;
29;"U2";"ESP-WROOM-32D-NARROW";1;"ESP-WROOM-3232D-NARROW";;;
30;"U$73";"VB1";1;"";;;
31;"U$68";"A03";1;"";;;
32;"U$26";"STAT0";1;"";;;
33;"D5";"WS2812-2020";1;"WS2812";;;
34;"U4";"DFN-8";1;"MAX17048";;;
35;"U7";"SO016";1;"CH340C";;;
36;"U$12";"SFE_LOGO_FLAME_.1";1;"";;;
37;"R6";"0603";1;"2.0k";;;
38;"D3";"LED-0603";1;"BLUE";;;
39;"J4";"JST-2-SMD";1;"";;;
40;"U3,U5";"SOT23-5";2;"XC6222B331MR-G";;;
41;"S3";"TACTILE_SWITCH_SMD_4.6X2.8MM";1;"Boot";;;
42;"Q3";"SOT23-3";1;"20V/4.2A/52mΩ/1.4W";;;
43;"U$71";"A30";1;"";;;
44;"Q2";"SC70-6";1;"MBT3904DW1T1";;;
45;"U$107";"NC0";1;"";;;
46;"U$79,U$109";"#RST#0";2;"";;;
47;"J3";"JST04_1MM_RA";1;"QWIIC_RA";;;
48;"U$25";"PWR2";1;"";;;
49;"FD3,FD1,FD4,FD2";"FIDUCIAL-MICRO";4;"FIDUCIALUFIDUCIAL";;;
50;"U$8";"#SHLD#0";1;"";;;
51;"U$94";"#32#8";1;"";;;
52;"U$86";"#25#A1#2";1;"";;;
53;"U$11";"#_3V3#0";1;"";;;
54;"U$95";"#33#6";1;"";;;
55;"JP2,JP1,JP3";"SMT-JUMPER_2_NC_TRACE_SILK";3;"JUMPER-SMT_2_NC_TRACE_SILK";;;
56;"LOGO2";"OSHW-LOGO-MINI";1;"OSHW-LOGOMINI";;;
57;"LOGO1";"SFE_LOGO_NAME_FLAME_.1";1;"SFE_LOGO_NAME_FLAME.1_INCH";;;
58;"U$4";"#4#FREE#0";1;"";;;
59;"U$10";"#_NC#0";1;"";;;
60;"U$89";"#39#A3#0";1;"";;;
61;"U$99";"#13#LED#0";1;"";;;
62;"U$96";"#EN#1";1;"";;;
63;"U$102";"#PWR#0";1;"";;;
64;"U$5";"#CHG_LED#0";1;"";;;
65;"TP2,TP1,TP3,TP4";"PAD.03X.05";4;"TEST-POINT3X5";;;
66;"J2";"MICROSD_TINY";1;"MICRO-SDFRICTION";;;
67;"U$92";"#15#7";1;"";;;
68;"U$2";"#23#PICO#0";1;"";;;
69;"U$90";"#12#4";1;"";;;
70;"U$7";"THING_PLUS_C0";1;"";;;
71;"U$98";"#VUSB#2";1;"";;;
72;"U$9";"#_GND#0";1;"";;;
73;"U$93";"#27#5";1;"";;;
74;"U$87";"#26#A0#3";1;"";;;
75;"U$84";"#35#A5#0";1;"";;;
76;"U$6";"ESP32#WROOM0";1;"";;;
77;"U$100";"#21#SDA#1";1;"";;;
78;"U$101";"#22#SCL#0";1;"";;;
79;"U$97";"#VBAT#0";1;"";;;
80;"U$83";"#18#SCK#0";1;"";;;
81;"U$81";"#16#RX#0";1;"";;;
82;"U$91";"#14#9";1;"";;;
83;"U$1";"SFE_LOGO_FLAME_STOP_.1";1;"";;;
84;"U$3";"#19#POCI#0";1;"";;;
85;"U$85";"#36#A4#0";1;"";;;
86;"U$72";"#17#TX#0";1;"";;;
87;"U$88";"#34#A2#1";1;"";;;

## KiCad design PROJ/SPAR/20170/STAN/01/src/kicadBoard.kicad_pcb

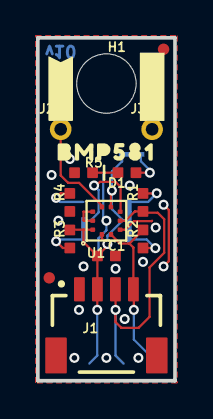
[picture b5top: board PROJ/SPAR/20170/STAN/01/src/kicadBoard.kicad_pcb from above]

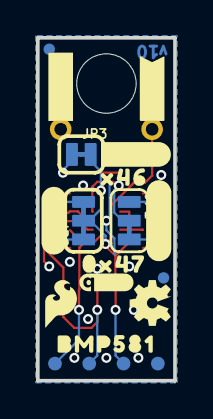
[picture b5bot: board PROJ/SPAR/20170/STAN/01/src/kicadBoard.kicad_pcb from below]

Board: 2 copper layers, 7.6 x 19.0 mm, 39 parts (20 on the bottom side), 12 nets.

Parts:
C1: 0.1uF; 0402-TIGHT
D1: RED; LED-0402
FD1, FD2, FD3, FD4: FIDUCIALUFIDUCIAL; FIDUCIAL-MICRO
FRAME1: FRAME-LETTER; CREATIVE_COMMONS
H1: STAND-OFF
J1: QWIIC_RIGHT_ANGLE; JST04_1MM_RA
J2, J3: 1X01_1MM_NO_SILK
JP1: ADR; SMT-JUMPER_3_1-NC_TRACE_SILK
JP2: I2C; SMT-JUMPER_3_2-NC_TRACE_SILK
JP3: LED; SMT-JUMPER_2_NC_TRACE_SILK
LOGO1: OSHW-LOGOMINI; OSHW-LOGO-MINI
LOGO2: SFE_LOGO_FLAME.1_INCH; SFE_LOGO_FLAME_.1
LOGO3: QWIIC_LOGO_3MM; QWIIC_3MM
LOGO4: SFE_LOGO_NAMEBLANK; BLANK
R1, R2: 2.2k; 0402-TIGHT
R3, R4: 10K; 0402-TIGHT
R5: 1k; 0402-TIGHT
TP1, TP2, TP3, TP4: TEST-POINT3; PAD.03X.03
U1: BMP581
U$1, U$2: BMP5810
U$3: #I2C#0
U$4: #ADR#0
U$5, U$6: #GND#0
U$7, U$8: #INT#0
U$9: #LED#0
U$10: X460
U$11: 0X470

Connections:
ADR: JP1.2, U1.5
GND: C1.2, J1.1, J3.1, R4.1, R5.1, TP1.1, U1.3, U1.8, U1.9
INT: J2.1, U1.7
unnamed: JP1.3, R3.1
unnamed: JP1.1, R4.2
unnamed: JP2.1, R2.1
unnamed: JP2.3, R1.2
unnamed: D1.A, JP3.1
unnamed: D1.C, R5.2
SCL: J1.4, R2.2, TP4.1, U1.2
SDA: J1.3, R1.1, TP3.1, U1.4
VDD: C1.1, J1.2, JP2.2, JP3.2, R3.2, TP2.1, U1.1, U1.6, U1.10

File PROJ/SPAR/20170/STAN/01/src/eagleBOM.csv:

"Part";"Value";"Device";"Package";"Description";"DESIGNER";"PROD_ID";"REV";"VALUE";
"C1";"0.1uF";"0.1UF-0402T-6.3V-10%-X7R";"0402-TIGHT";"0.1µF ceramic capacitors";"";"CAP-14993";"";"0.1uF";
"D1";"RED";"LED-RED_0402";"LED-0402";"Red SMD LED";"";"DIO-16757";"";"RED";
"FD1";"FIDUCIALUFIDUCIAL";"FIDUCIALUFIDUCIAL";"FIDUCIAL-MICRO";"Fiducial Alignment Points";"";"";"";"";
"FD2";"FIDUCIALUFIDUCIAL";"FIDUCIALUFIDUCIAL";"FIDUCIAL-MICRO";"Fiducial Alignment Points";"";"";"";"";
"FD3";"FIDUCIALUFIDUCIAL";"FIDUCIALUFIDUCIAL";"FIDUCIAL-MICRO";"Fiducial Alignment Points";"";"";"";"";
"FD4";"FIDUCIALUFIDUCIAL";"FIDUCIALUFIDUCIAL";"FIDUCIAL-MICRO";"Fiducial Alignment Points";"";"";"";"";
"FRAME1";"FRAME-LETTER";"FRAME-LETTER";"CREATIVE_COMMONS";"Schematic Frame - Letter";"";"";"";"";
"H1";"STAND-OFF";"STAND-OFF";"STAND-OFF";"Stand Off";"";"";"";"";
"J1";"QWIIC_RIGHT_ANGLE";"QWIIC_CONNECTORJS-1MM";"JST04_1MM_RA";"SparkFun I2C Standard Qwiic Connector";"";"CONN-13694";"";"QWIIC_RIGHT_ANGLE";
"J2";"";"CONN_01_1MM";"1X01_1MM_NO_SILK";"Single connection point. Often used as Generic Header-pin footprint for 0.1 inch spaced/style header connections";"";"";"";"";
"J3";"";"CONN_01_1MM";"1X01_1MM_NO_SILK";"Single connection point. Often used as Generic Header-pin footprint for 0.1 inch spaced/style header connections";"";"";"";"";
"JP1";"ADR";"JUMPER-SMT_3_1-NC_TRACE_SILK";"SMT-JUMPER_3_1-NC_TRACE_SILK";"Normally closed trace jumper (1 of 2 connections)";"";"";"";"";
"JP2";"I2C";"JUMPER-SMT_3_2-NC_TRACE_SILK";"SMT-JUMPER_3_2-NC_TRACE_SILK";"Normally closed trace jumper (2 of 2 connections)";"";"";"";"";
"JP3";"LED";"JUMPER-SMT_2_NC_TRACE_SILK";"SMT-JUMPER_2_NC_TRACE_SILK";"Normally closed trace jumper";"";"";"";"";
"LOGO1";"OSHW-LOGOMINI";"OSHW-LOGOMINI";"OSHW-LOGO-MINI";"Open-Source Hardware (OSHW) Logo";"";"";"";"";
"LOGO2";"SFE_LOGO_FLAME.1_INCH";"SFE_LOGO_FLAME.1_INCH";"SFE_LOGO_FLAME_.1";"SparkFun Flame Logo";"";"";"";"";
"LOGO3";"QWIIC_LOGO_3MM";"QWIIC_LOGO_3MM";"QWIIC_3MM";"Qwiic Logos for placement on schematic and PCB. The 5.5mm silk logo is best for placing next to Qwiic connector.";"";"";"";"";
"LOGO4";"SFE_LOGO_NAMEBLANK";"SFE_LOGO_NAMEBLANK";"BLANK";"SparkFun Font Logo";"";"";"";"";
"R1";"2.2k";"2.2KOHM-0402T-1/16W-1%";"0402-TIGHT";"2.2kΩ resistor";"";"RES-14341";"";"2.2k";
"R2";"2.2k";"2.2KOHM-0402T-1/16W-1%";"0402-TIGHT";"2.2kΩ resistor";"";"RES-14341";"";"2.2k";
"R3";"10K";"10KOHM-0402-1/10W-0.1%";"0402-TIGHT";"10kΩ resistor";"";"RES-16147";"";"10K";
"R4";"10K";"10KOHM-0402-1/10W-0.1%";"0402-TIGHT";"10kΩ resistor";"";"RES-16147";"";"10K";
"R5";"1k";"1KOHM-0402T-1/16W-1%";"0402-TIGHT";"1kΩ resistor";"";"RES-14342";"";"1k";
"TP1";"TEST-POINT3";"TEST-POINT3";"PAD.03X.03";"SparkFun Test Points";"";"";"";"";
"TP2";"TEST-POINT3";"TEST-POINT3";"PAD.03X.03";"SparkFun Test Points";"";"";"";"";
"TP3";"TEST-POINT3";"TEST-POINT3";"PAD.03X.03";"SparkFun Test Points";"";"";"";"";
"TP4";"TEST-POINT3";"TEST-POINT3";"PAD.03X.03";"SparkFun Test Points";"";"";"";"";
"U1";"BMP581";"BMP581";"BMP581";"Bosch BMP581 Pressure Sensor";"";"IC-16798";"";"";

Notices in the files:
parts and their libraries:
HTTPS://CREATIVECOMMONS.ORG/LICENSES/BY-SA/4.0
RELEASED UNDER THE CREATIVE COMMONS ATTRIBUTION SHARE-ALIKE 4.0 LICENSE
